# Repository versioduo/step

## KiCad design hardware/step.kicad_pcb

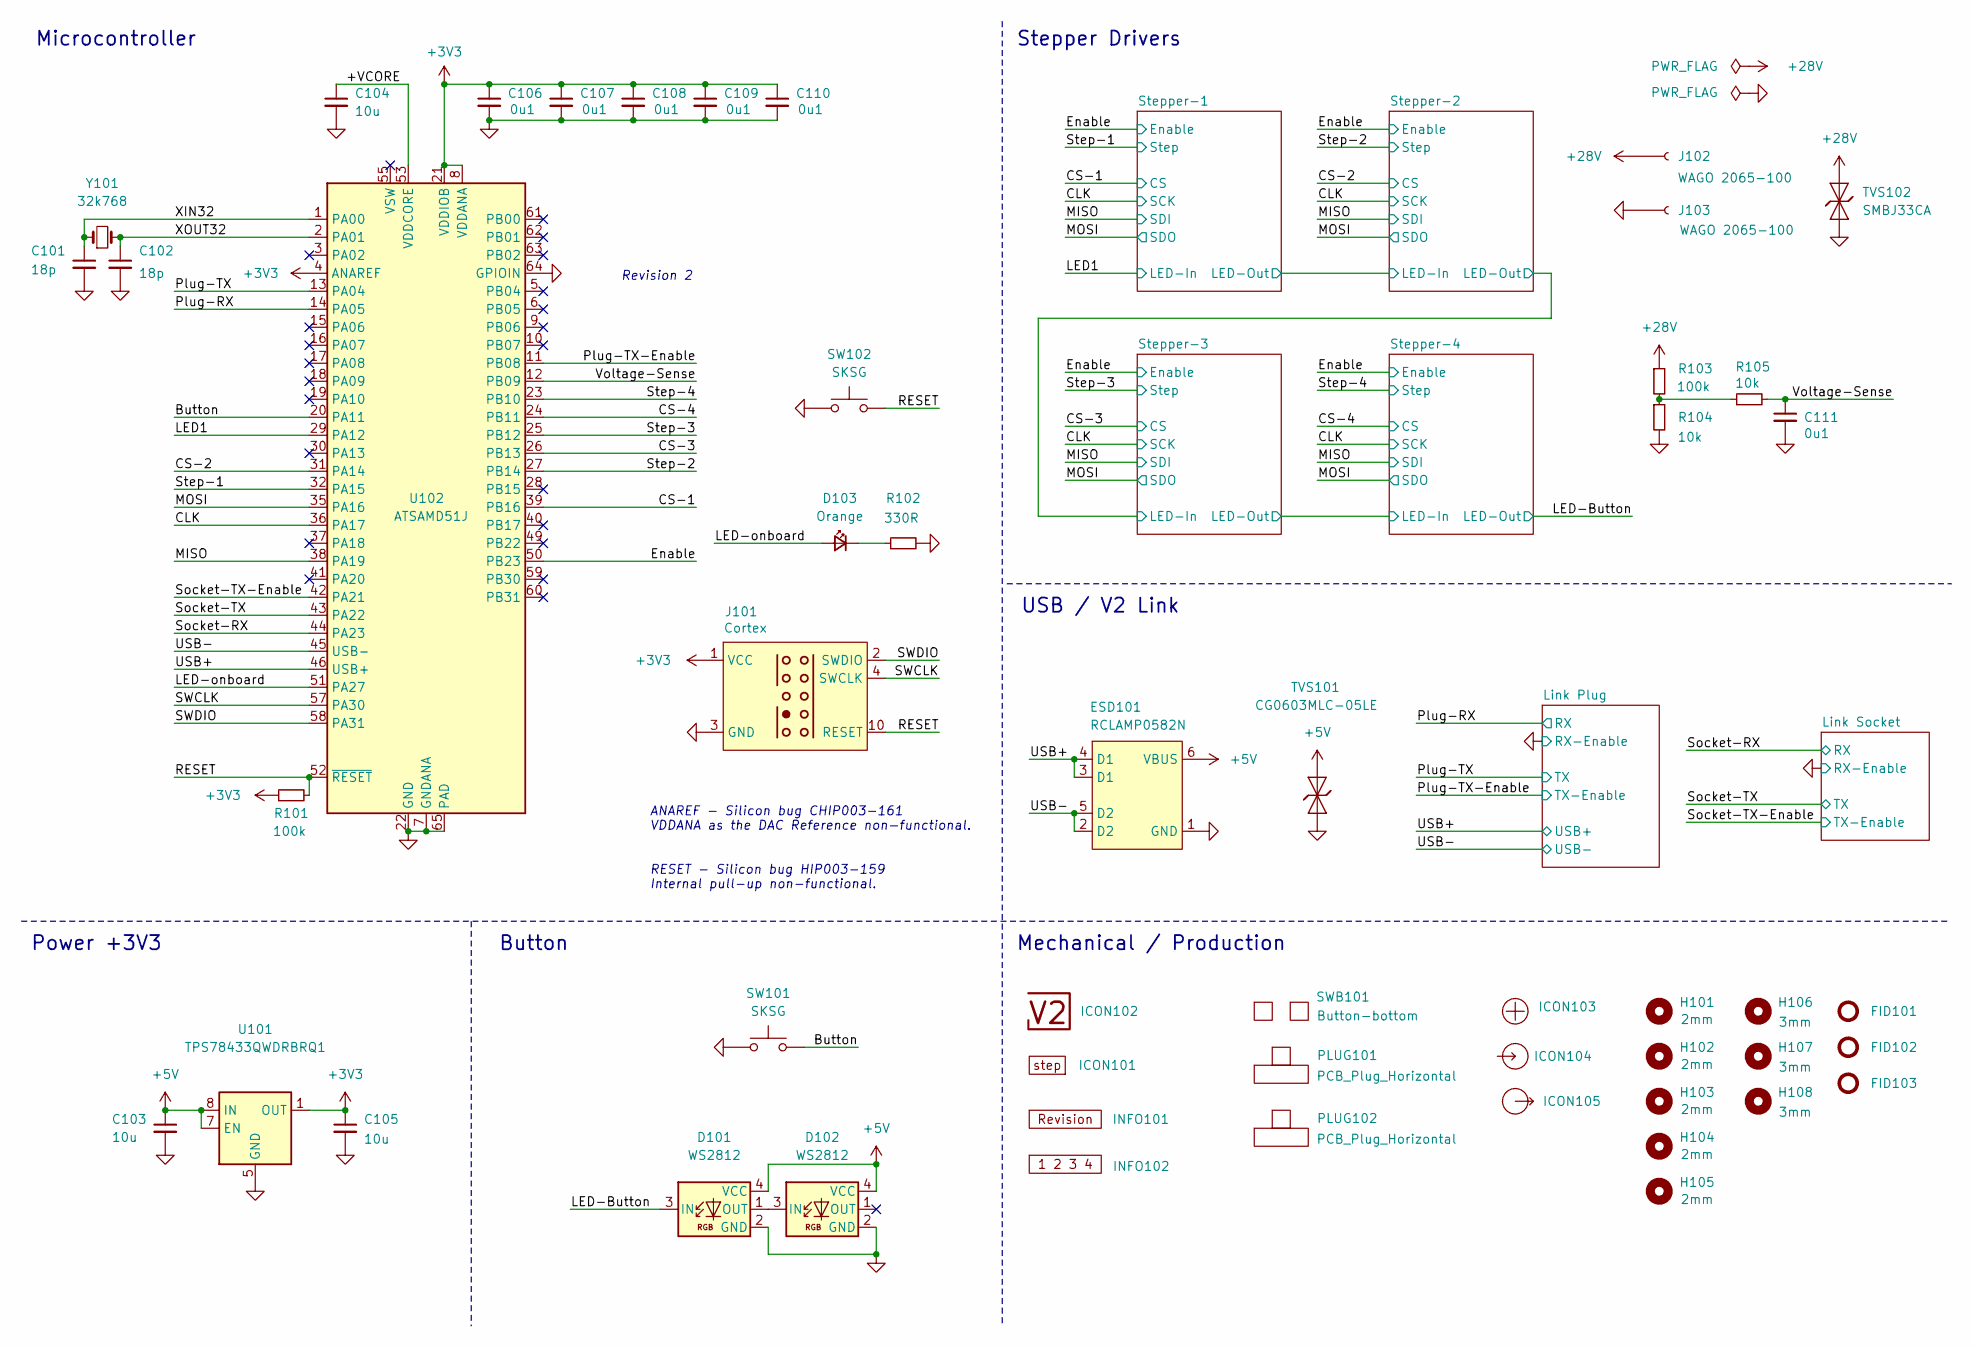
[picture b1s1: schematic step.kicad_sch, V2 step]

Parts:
C101, C102: 18p; C_1608; Rating 50V; Mouser 810-CGA3E2C0G1H180J
C103, C105: 10u; C_2012; Rating 25V; Mouser 810-C2012X5R1E106K
C104: 10u; C_1608; Rating 10V; Mouser 810-C1608X6S1A106M
C106, C107, C108, C109, C110, C111: 0u1; C_1608; Rating 50V; Mouser 810-CGA3E2X7R1H104MA
D101, D102: WS2812; WS2812-2020; Rating 15mA; LCSC C965555
D103: Orange; LED_1608; Rating 605nm; Mouser 755-SML-D12D1WT86
ESD101: RCLAMP0582N; SLP1210N6; Rating 20kV; Mouser 947-RCLAMP0582N.TCT
FID101, FID102, FID103: Fiducial_Paste; Fiducial_0.5mm_Mask1mm_Paste
H101, H102, H103, H104, H105: 2mm; MountingHole_2mm
H106, H107, H108: 3mm; MountingHole_3mm
ICON101: Board_step; Board_step_Small
ICON102: V2-logo; Logo_Small
ICON103: Plus; Plus_Small
ICON104: Arrow_In
ICON105: Arrow_Out
INFO101: Revision
INFO102: Layer_Numbers-6
J101: Cortex
J102, J103: WAGO 2065-100; 2065-100; Rating 9A
PLUG101, PLUG102: PCB_Plug_Horizontal
R101, R103: 100k; R_1608; Rating 100mW; Mouser 71-CRCW0603100KFKEAC
R102: 330R; R_1608; Rating 100mW; Mouser 71-CRCW0603330RFKEAC
R104, R105: 10k; R_1608; Rating 100mW; Mouser 71-CRCW060310K0FKEAC
SW101, SW102: SKSG; Rating 1.6N; Mouser 688-SKSGACE010
SWB101: Button-bottom; PCB_Button-bottom
TVS101: CG0603MLC-05LE; D_1608; Rating 5V; Mouser 652-CG0603MLC-05LE
TVS102: SMBJ33CA; D_SMB; Rating 33V; Mouser 652-SMBJ33CA-Q
U101: TPS78433QWDRBRQ1; VSON-8-1_3x3mm_P0.65_EP1.65x2.4mm; Rating 300mA; Mouser 595-TPS78433QWDRBRQ1
U102: ATSAMD51J; QFN-64-1EP_9x9mm_P0.5mm_EP4.8x4.8mm_ThermalVias; Rating Cortex-M4F; Mouser 556-ATSAMD51J19AMU
Y101: 32k768; Crystal_SMD_3215-2Pin_3.2x1.5mm; Rating 10ppm; Mouser 815-ABS0716632.768KT

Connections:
+3V3: C105.1, C106.1, C107.1, C108.1, C109.1, C110.1, J101.1 (VCC), R101.1, U101.1 (OUT), U102.4 (ANAREF), U102.8 (VDDANA), U102.21 (VDDIOB), U102.34 (VDDIO), U102.48 (VDDIO), U102.56 (VDDIO); also elsewhere on the board
+5V: C103.1, D101.4 (VCC), D102.4 (VCC), ESD101.6 (VBUS), TVS101.2 (A), U101.6 (EN), U101.7 (EN), U101.8 (IN); also elsewhere on the board
+28V: J102.1, R103.1, TVS102.2 (A); also elsewhere on the board
/+VCORE: C104.1, U102.53 (VDDCORE)
/Button: SW101.2, U102.20 (PA11)
/CLK: U102.36 (PA17); also elsewhere on the board
/CS-1: U102.39 (PB16); also elsewhere on the board
/CS-2: U102.31 (PA14); also elsewhere on the board
/CS-3: U102.26 (PB13); also elsewhere on the board
/CS-4: U102.24 (PB11); also elsewhere on the board
/Enable: U102.50 (PB23); also elsewhere on the board
/LED1: U102.29 (PA12); also elsewhere on the board
/LED-Button: D101.3 (IN); also elsewhere on the board
/LED-onboard: D103.2 (A), U102.51 (PA27)
/MISO: U102.38 (PA19); also elsewhere on the board
/MOSI: U102.35 (PA16); also elsewhere on the board
/Plug-RX: U102.14 (PA05); also elsewhere on the board
/Plug-TX: U102.13 (PA04); also elsewhere on the board
/Plug-TX-Enable: U102.11 (PB08); also elsewhere on the board
/RESET: J101.10 (RESET), R101.2, SW102.2, U102.52 (~RESET)
/SWCLK: J101.4 (SWCLK), U102.57 (PA30)
/SWDIO: J101.2 (SWDIO), U102.58 (PA31)
/Socket-RX: U102.44 (PA23); also elsewhere on the board
/Socket-TX: U102.43 (PA22); also elsewhere on the board
/Socket-TX-Enable: U102.42 (PA21); also elsewhere on the board
/Step-1: U102.32 (PA15); also elsewhere on the board
/Step-2: U102.27 (PB14); also elsewhere on the board
/Step-3: U102.25 (PB12); also elsewhere on the board
/Step-4: U102.23 (PB10); also elsewhere on the board
/USB+: ESD101.3 (D1), ESD101.4 (D1), U102.46 (USB+); also elsewhere on the board
/USB-: ESD101.2 (D2), ESD101.5 (D2), U102.45 (USB-); also elsewhere on the board
/Voltage-Sense: C111.1, R105.2, U102.12 (PB09)
/XIN32: C101.1, U102.1 (PA00), Y101.1
/XOUT32: C102.1, U102.2 (PA01), Y101.2
GND: C101.2, C102.2, C103.2, C104.2, C105.2, C106.2, C107.2, C108.2, C109.2, C110.2, C111.2, D101.2 (GND), D102.2 (GND), ESD101.1 (GND), J101.3 (GND), J101.5 (GND), J103.1, R102.2, R104.2, SW101.1, SW102.1, TVS101.1 (K), TVS102.1 (K), U101.5 (GND), U101.9 (GND), U102.7 (GNDANA), U102.22 (GND), U102.33 (GND), U102.47 (GND), U102.54 (GND), U102.64 (GPIOIN), U102.65 (PAD); also elsewhere on the board
unnamed: D101.1 (OUT), D102.3 (IN)
unnamed: D103.1 (K), R102.1
unnamed: R103.2, R104.1, R105.1

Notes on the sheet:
﻿ANAREF - Silicon bug CHIP003-161 VDDANA as the DAC Reference non-functional.
Stepper Drivers
RESET - ﻿Silicon bug HIP003-159 Internal pull-up non-functional.
Button
Revision 2
USB / V2 Link
Mechanical / Production
Power +3V3
Microcontroller

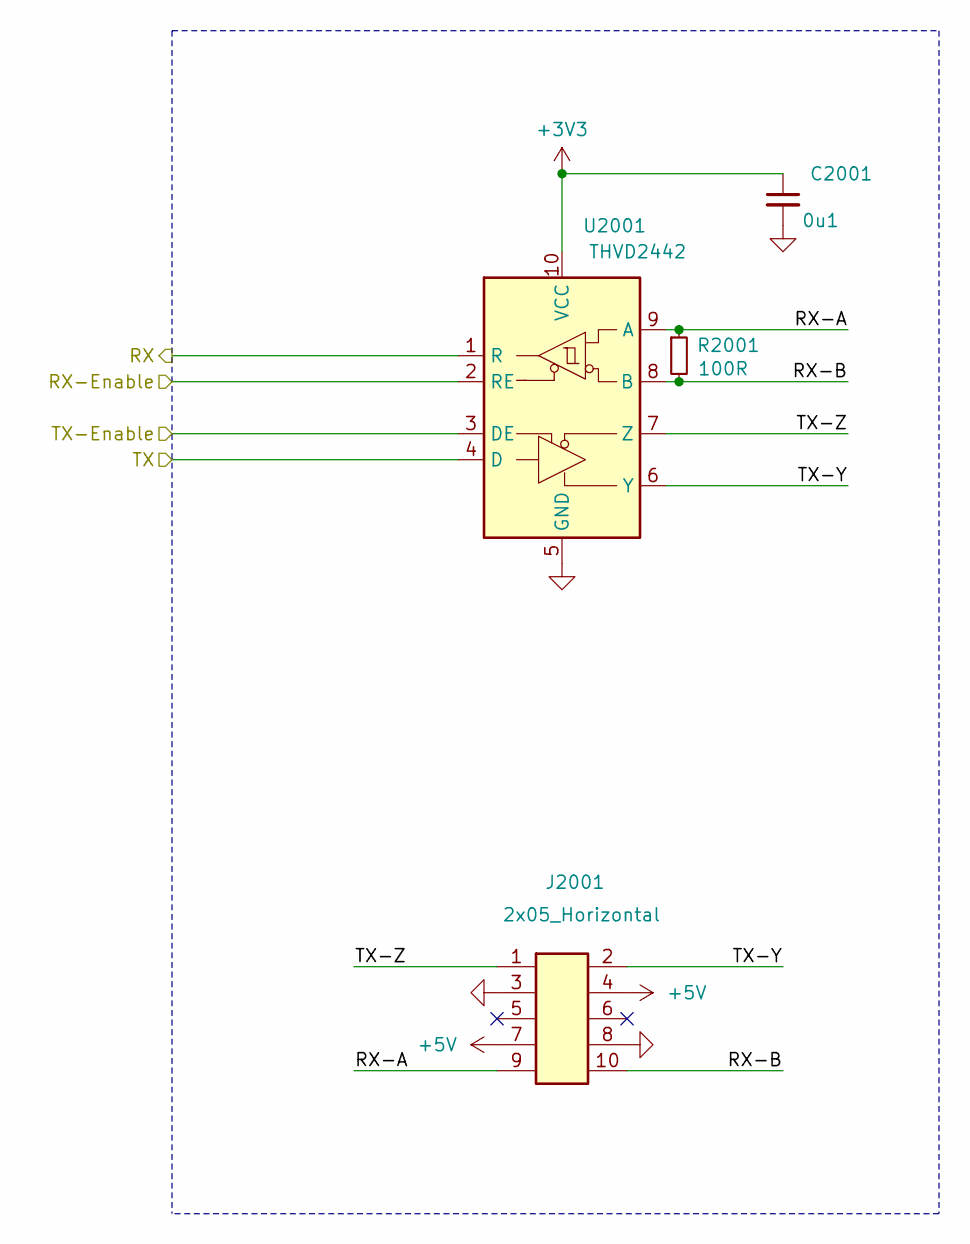
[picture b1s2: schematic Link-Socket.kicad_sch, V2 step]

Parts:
C2001: 0u1; C_1608; Rating 50V; Mouser 810-CGA3E2X7R1H104MA
J2001: 2x05_Horizontal; PinHeader_2x05_P1.27mm_Horizontal; Rating 1A; Mouser 649-200211120001T4LF
R2001: 100R; R_1608; Rating 330mW; Mouser 71-CRCW0603100RFKEAH
U2001: THVD2442; VSON-10-4-1EP_3x3mm_P0.5mm_EP1.65x2.4mm_ThermalVias; Rating 20Mbps; Mouser 595-THVD2442DRCR

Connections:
+3V3: C2001.1, U2001.10 (VCC); also elsewhere on the board
+5V: J2001.4, J2001.7; also elsewhere on the board
/Link Socket/RX-A: J2001.9, R2001.1, U2001.9 (A)
/Link Socket/RX-B: J2001.10, R2001.2, U2001.8 (B)
/Link Socket/TX-Y: J2001.2, U2001.6 (Y)
/Link Socket/TX-Z: J2001.1, U2001.7 (Z)
/Socket-RX: U2001.1 (R); also elsewhere on the board
/Socket-TX: U2001.4 (D); also elsewhere on the board
/Socket-TX-Enable: U2001.3 (DE); also elsewhere on the board
GND: C2001.2, J2001.3, J2001.8, U2001.2 (RE), U2001.5 (GND), U2001.11 (GND); also elsewhere on the board

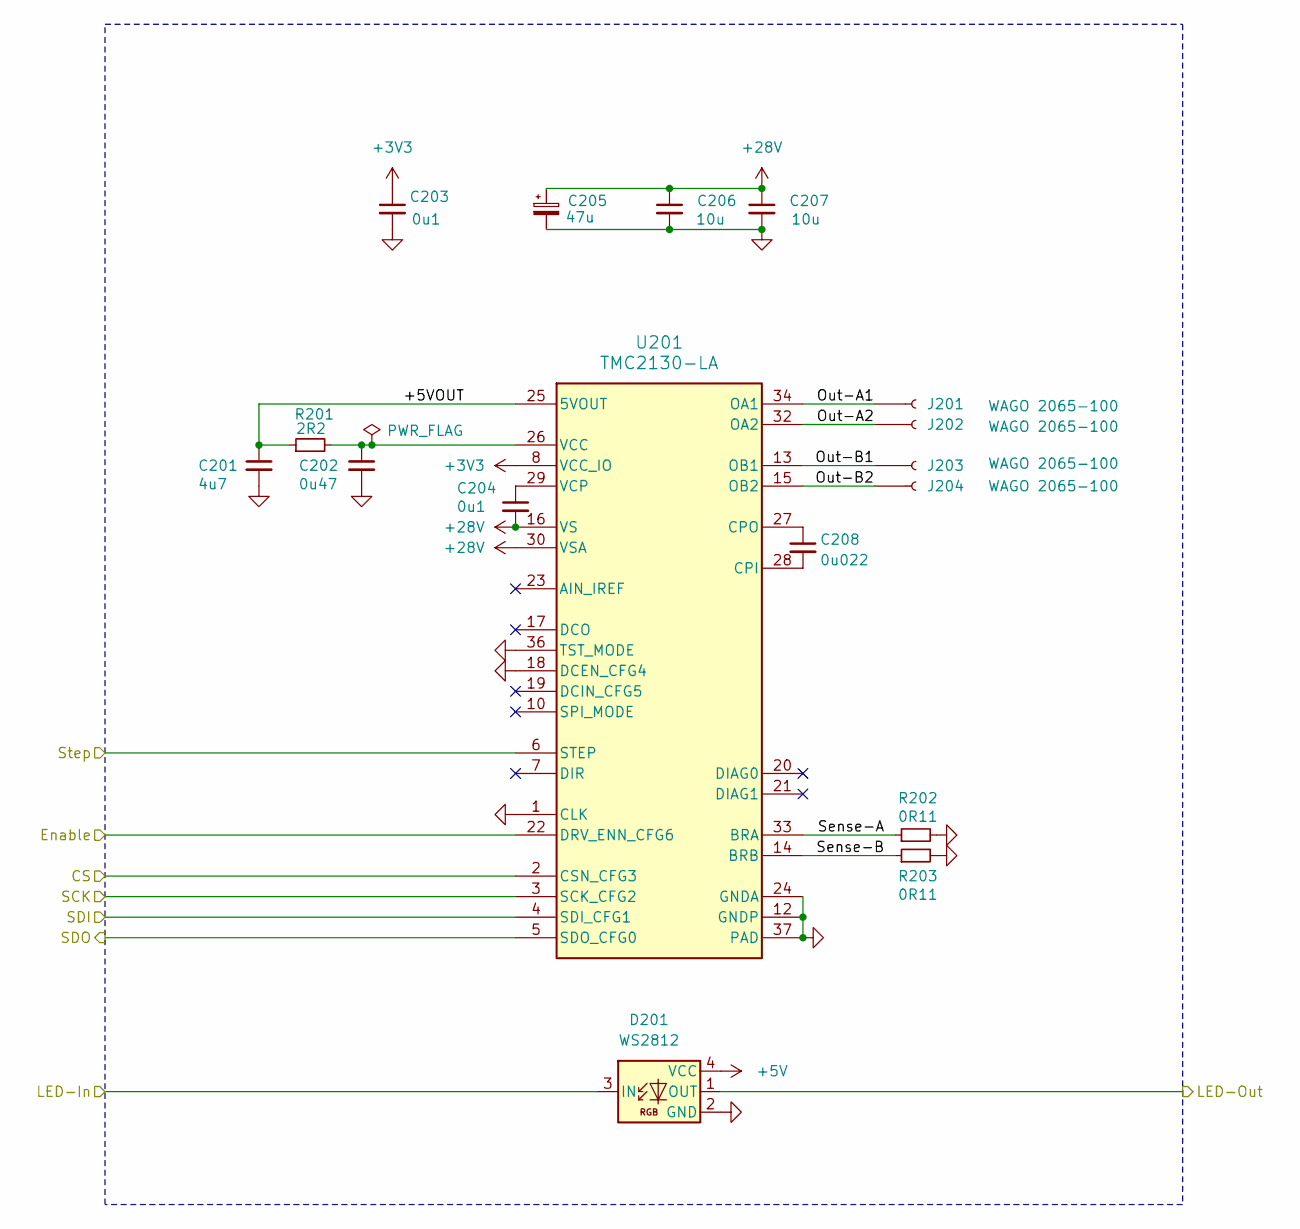
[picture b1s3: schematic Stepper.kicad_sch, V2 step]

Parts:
C201: 4u7; C_1608; Rating 10V; Mouser 603-CC603KRX5R6BB475
C202: 0u47; C_1608; Rating 50V; Mouser 810-CGA3E3X7R1H474KB
C203, C204: 0u1; C_1608; Rating 50V; Mouser 810-CGA3E2X7R1H104MA
C205: 47u; CP_Elec_6.3x5.8; Rating 35V; Mouser 667-EEE-FK1V470P
C206, C207: 10u; C_3225; Rating 50V; Mouser 810-CNC6P1X7R1H106K2
C208: 0u022; C_1608; Rating 50V; Mouser 603-CC603KPX7R9BB223
D201: WS2812; WS2812-2020; Rating 15mA; LCSC C965555
J201, J202, J203, J204: WAGO 2065-100; 2065-100; Rating 9A
R201: 2R2; R_1608; Rating 500mW; Mouser 71-RCS06032R20JNEA
R202, R203: 0R11; R_2012; Rating 500mW; Mouser 667-ERJ-6DSFR11V
U201: TMC2130-LA; QFN-36-5X6; Rating 2A; LCSC C915795

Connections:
+3V3: C203.1, U201.8 (VCC_IO); also elsewhere on the board
+5V: D201.4 (VCC); also elsewhere on the board
+28V: C204.2, C205.1, C206.1, C207.1, U201.16 (VS), U201.30 (VSA), U201.31 (VS); also elsewhere on the board
/CLK: U201.3 (SCK_CFG2); also elsewhere on the board
/CS-1: U201.2 (CSN_CFG3); also elsewhere on the board
/Enable: U201.22 (DRV_ENN_CFG6); also elsewhere on the board
/LED1: D201.3 (IN); also elsewhere on the board
/MISO: U201.4 (SDI_CFG1); also elsewhere on the board
/MOSI: U201.5 (SDO_CFG0); also elsewhere on the board
/Step-1: U201.6 (STEP); also elsewhere on the board
/Stepper-1/+5VOUT: C201.1, R201.1, U201.25 (5VOUT)
/Stepper-1/LED-Out: D201.1 (OUT); also elsewhere on the board
/Stepper-1/Out-A1: J201.1, U201.34 (OA1)
/Stepper-1/Out-A2: J202.1, U201.32 (OA2)
/Stepper-1/Out-B1: J203.1, U201.13 (OB1)
/Stepper-1/Out-B2: J204.1, U201.15 (OB2)
/Stepper-1/Sense-A: R202.1, U201.33 (BRA)
/Stepper-1/Sense-B: R203.1, U201.14 (BRB)
GND: C201.2, C202.2, C203.2, C205.2, C206.2, C207.2, D201.2 (GND), R202.2, R203.2, U201.1 (CLK), U201.12 (GNDP), U201.18 (DCEN_CFG4), U201.24 (GNDA), U201.35 (GNDP), U201.36 (TST_MODE), U201.37 (PAD); also elsewhere on the board
unnamed: C208.2, U201.28 (CPI)
unnamed: C208.1, U201.27 (CPO)
unnamed: C202.1, R201.2, U201.26 (VCC)
unnamed: C204.1, U201.29 (VCP)

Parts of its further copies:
C301, C401, C501: 4u7; C_1608; Rating 10V; Mouser 603-CC603KRX5R6BB475
C302, C402, C502: 0u47; C_1608; Rating 50V; Mouser 810-CGA3E3X7R1H474KB
C303, C304, C403, C404, C503, C504: 0u1; C_1608; Rating 50V; Mouser 810-CGA3E2X7R1H104MA
C305, C405, C505: 47u; CP_Elec_6.3x5.8; Rating 35V; Mouser 667-EEE-FK1V470P
C306, C307, C406, C407, C506, C507: 10u; C_3225; Rating 50V; Mouser 810-CNC6P1X7R1H106K2
C308, C408, C508: 0u022; C_1608; Rating 50V; Mouser 603-CC603KPX7R9BB223
D301, D401, D501: WS2812; WS2812-2020; Rating 15mA; LCSC C965555
J301, J302, J303, J304, J401, J402, J403, J404, J501, J502, J503, J504: WAGO 2065-100; 2065-100; Rating 9A
R301, R401, R501: 2R2; R_1608; Rating 500mW; Mouser 71-RCS06032R20JNEA
R302, R303, R402, R403, R502, R503: 0R11; R_2012; Rating 500mW; Mouser 667-ERJ-6DSFR11V
U301, U401, U501: TMC2130-LA; QFN-36-5X6; Rating 2A; LCSC C915795

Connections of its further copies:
+3V3: C303.1, C403.1, C503.1, U301.8 (VCC_IO), U401.8 (VCC_IO), U501.8 (VCC_IO); also elsewhere on the board
+5V: D301.4 (VCC), D401.4 (VCC), D501.4 (VCC); also elsewhere on the board
+28V: C304.2, C305.1, C306.1, C307.1, C404.2, C405.1, C406.1, C407.1, C504.2, C505.1, C506.1, C507.1, U301.16 (VS), U301.30 (VSA), U301.31 (VS), U401.16 (VS), U401.30 (VSA), U401.31 (VS), U501.16 (VS), U501.30 (VSA), U501.31 (VS); also elsewhere on the board
/CLK: U301.3 (SCK_CFG2), U401.3 (SCK_CFG2), U501.3 (SCK_CFG2); also elsewhere on the board
/CS-2: U301.2 (CSN_CFG3); also elsewhere on the board
/CS-3: U401.2 (CSN_CFG3); also elsewhere on the board
/CS-4: U501.2 (CSN_CFG3); also elsewhere on the board
/Enable: U301.22 (DRV_ENN_CFG6), U401.22 (DRV_ENN_CFG6), U501.22 (DRV_ENN_CFG6); also elsewhere on the board
/LED-Button: D501.1 (OUT); also elsewhere on the board
/MISO: U301.4 (SDI_CFG1), U401.4 (SDI_CFG1), U501.4 (SDI_CFG1); also elsewhere on the board
/MOSI: U301.5 (SDO_CFG0), U401.5 (SDO_CFG0), U501.5 (SDO_CFG0); also elsewhere on the board
/Step-2: U301.6 (STEP); also elsewhere on the board
/Step-3: U401.6 (STEP); also elsewhere on the board
/Step-4: U501.6 (STEP); also elsewhere on the board
/Stepper-1/LED-Out: D301.3 (IN); also elsewhere on the board
/Stepper-2/+5VOUT: C301.1, R301.1, U301.25 (5VOUT)
/Stepper-2/LED-Out: D301.1 (OUT), D401.3 (IN)
/Stepper-2/Out-A1: J301.1, U301.34 (OA1)
/Stepper-2/Out-A2: J302.1, U301.32 (OA2)
/Stepper-2/Out-B1: J303.1, U301.13 (OB1)
/Stepper-2/Out-B2: J304.1, U301.15 (OB2)
/Stepper-2/Sense-A: R302.1, U301.33 (BRA)
/Stepper-2/Sense-B: R303.1, U301.14 (BRB)
/Stepper-3/+5VOUT: C401.1, R401.1, U401.25 (5VOUT)
/Stepper-3/LED-Out: D401.1 (OUT), D501.3 (IN)
/Stepper-3/Out-A1: J401.1, U401.34 (OA1)
/Stepper-3/Out-A2: J402.1, U401.32 (OA2)
/Stepper-3/Out-B1: J403.1, U401.13 (OB1)
/Stepper-3/Out-B2: J404.1, U401.15 (OB2)
/Stepper-3/Sense-A: R402.1, U401.33 (BRA)
/Stepper-3/Sense-B: R403.1, U401.14 (BRB)
/Stepper-4/+5VOUT: C501.1, R501.1, U501.25 (5VOUT)
/Stepper-4/Out-A1: J501.1, U501.34 (OA1)
/Stepper-4/Out-A2: J502.1, U501.32 (OA2)
/Stepper-4/Out-B1: J503.1, U501.13 (OB1)
/Stepper-4/Out-B2: J504.1, U501.15 (OB2)
/Stepper-4/Sense-A: R502.1, U501.33 (BRA)
/Stepper-4/Sense-B: R503.1, U501.14 (BRB)
GND: C301.2, C302.2, C303.2, C305.2, C306.2, C307.2, C401.2, C402.2, C403.2, C405.2, C406.2, C407.2, C501.2, C502.2, C503.2, C505.2, C506.2, C507.2, D301.2 (GND), D401.2 (GND), D501.2 (GND), R302.2, R303.2, R402.2, R403.2, R502.2, R503.2, U301.1 (CLK), U301.12 (GNDP), U301.18 (DCEN_CFG4), U301.24 (GNDA), U301.35 (GNDP), U301.36 (TST_MODE), U301.37 (PAD), U401.1 (CLK), U401.12 (GNDP), U401.18 (DCEN_CFG4), U401.24 (GNDA), U401.35 (GNDP), U401.36 (TST_MODE), U401.37 (PAD), U501.1 (CLK), U501.12 (GNDP), U501.18 (DCEN_CFG4), U501.24 (GNDA), U501.35 (GNDP), U501.36 (TST_MODE), U501.37 (PAD); also elsewhere on the board
unnamed: C308.2, U301.28 (CPI)
unnamed: C308.1, U301.27 (CPO)
unnamed: C302.1, R301.2, U301.26 (VCC)
unnamed: C304.1, U301.29 (VCP)
unnamed: C408.2, U401.28 (CPI)
unnamed: C408.1, U401.27 (CPO)
unnamed: C402.1, R401.2, U401.26 (VCC)
unnamed: C404.1, U401.29 (VCP)
unnamed: C508.2, U501.28 (CPI)
unnamed: C508.1, U501.27 (CPO)
unnamed: C502.1, R501.2, U501.26 (VCC)
unnamed: C504.1, U501.29 (VCP)

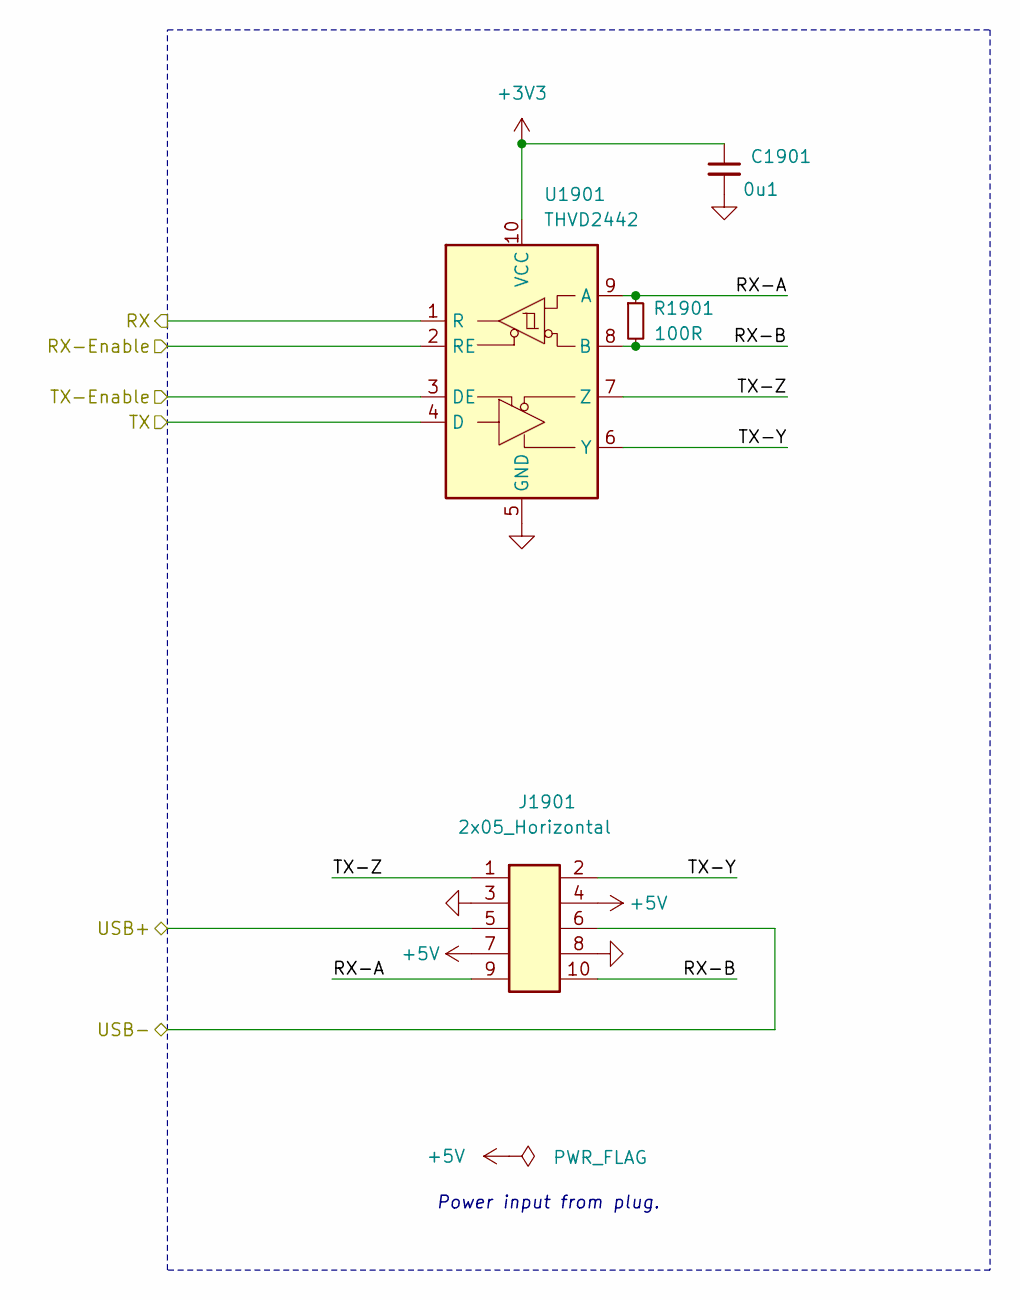
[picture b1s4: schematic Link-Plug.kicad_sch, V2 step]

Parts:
C1901: 0u1; C_1608; Rating 50V; Mouser 810-CGA3E2X7R1H104MA
J1901: 2x05_Horizontal; PinHeader_2x05_P1.27mm_Horizontal; Rating 1A; Mouser 649-200211120001T4LF
R1901: 100R; R_1608; Rating 330mW; Mouser 71-CRCW0603100RFKEAH
U1901: THVD2442; VSON-10-4-1EP_3x3mm_P0.5mm_EP1.65x2.4mm_ThermalVias; Rating 20Mbps; Mouser 595-THVD2442DRCR

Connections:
+3V3: C1901.1, U1901.10 (VCC); also elsewhere on the board
+5V: J1901.4, J1901.7; also elsewhere on the board
/Link Plug/RX-A: J1901.9, R1901.1, U1901.9 (A)
/Link Plug/RX-B: J1901.10, R1901.2, U1901.8 (B)
/Link Plug/TX-Y: J1901.2, U1901.6 (Y)
/Link Plug/TX-Z: J1901.1, U1901.7 (Z)
/Plug-RX: U1901.1 (R); also elsewhere on the board
/Plug-TX: U1901.4 (D); also elsewhere on the board
/Plug-TX-Enable: U1901.3 (DE); also elsewhere on the board
/USB+: J1901.5; also elsewhere on the board
/USB-: J1901.6; also elsewhere on the board
GND: C1901.2, J1901.3, J1901.8, U1901.2 (RE), U1901.5 (GND), U1901.11 (GND); also elsewhere on the board

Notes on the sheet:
Power input from plug.

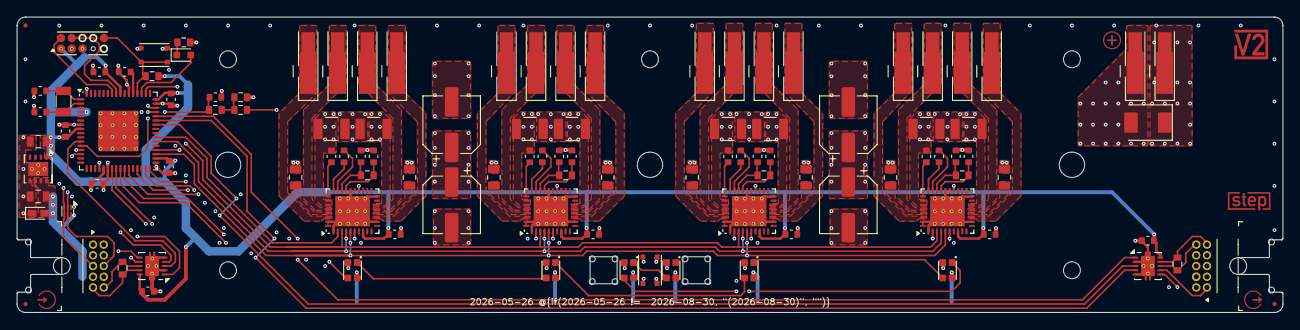
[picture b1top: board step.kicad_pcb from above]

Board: 6 copper layers, 150.0 x 35.0 mm, 127 parts (0 on the bottom side), 93 nets.

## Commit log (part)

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2021-09-24 Import
2024-01-21 ArduinoJson 7
2024-07-03 Update LVDS driver logic
2024-08-10 Coding Style
2025-12-29 Colour
2026-01-11 Update front + back
2026-01-12 Update parts library
2026-01-14 Update parts
2026-01-27 Refresh
2026-02-01 Update library
2026-02-10 Use date as revision
2026-02-13 Replace Order_Number
2026-03-12 Update sheet metal
2026-03-14 Update ESD suppressor
2026-03-21 KiCad 10
2026-05-11 Good Bye Imperial
2026-05-27 Switch to 6 layer
2026-06-21 Update MIDI API
2026-06-23 Update V2MIDI API
